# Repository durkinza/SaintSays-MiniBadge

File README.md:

# SAINTSays Mini-Badge

<span style="font-size:0.8em;font-style:italic;">This badge is not made in affiliation with or endorced by the SAINTCON conference or the Utah SAINT organization</span>

This was my first time designing and producing a minibadge for SAINTCON (2024), so it may be a bit rough around the edges.

This repo contains the Code and KiCad file for the SAINTSays Mini-Badge.

## Programming the Badge

Compiling the code in the Arduino IDE for an ATTINY requires a package that supports the `Wire.h` library.

I found that the [ATTINYCore](https://github.com/SpenceKonde/ATTinyCore/blob/v2.0.0-devThis-is-the-head-submit-PRs-against-this/Installation.md) library works well for this. 
If you don't plan on using the I2C features, The [attiny](https://github.com/damellis/attiny) package can also be used for programming the badge. 

The badge has the AREF pins connected to the Mini-Badge headers using the [suggested connection method](https://github.com/lukejenkins/minibadge#prog): 

| Header| Pin |
|-------|-------|
| MISO  | Pin 3 |
| CLK   | Pin 4 |
| MOSI  | Pin 5 |
| RESET | Pin 6 |

The power pin is wired to the 3.3v supply on Pin 7 and ground on Pin 8.

The Clock and SDA/SCL pins are also connected to the ATTiny. 
Be sure these Headers are not connected to external things when programming the badge. 

## Disabling I2C
If you don't plan on using the I2C features of the badbge, the code can be removed by commenting out the `#define USEI2C true` line near the top of the .ino file. 
This has the added benefit of making the compiled code a fair bit smaller too.

## Documentation

[How to solder the badge](https://zanedurk.in/soldering-the-saintsays-mini-badge/)

[How it's made](https://zanedurk.in/saintsays-mini-badge/)

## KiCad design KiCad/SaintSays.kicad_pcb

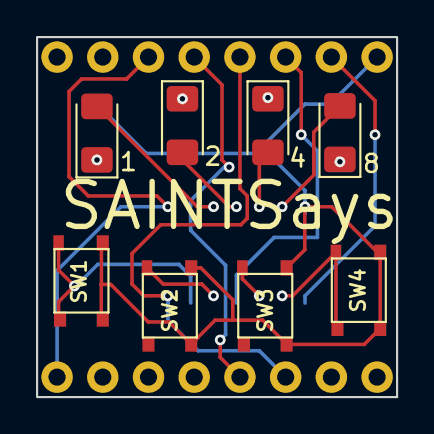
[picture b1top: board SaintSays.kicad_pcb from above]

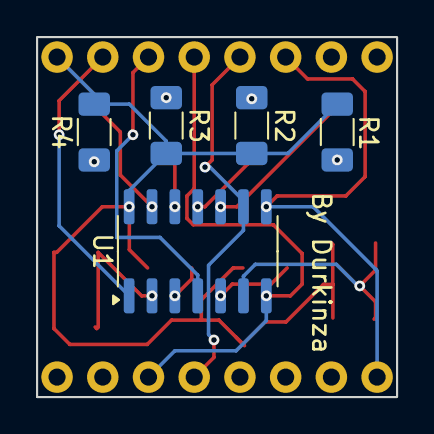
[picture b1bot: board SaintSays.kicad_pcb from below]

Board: 2 copper layers, 20.0 x 20.0 mm, 14 parts (5 on the bottom side), 18 nets.

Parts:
1, 2, 4, 8: LED; LED_1206_3216Metric_Pad1.42x1.75mm_HandSolder
MB1: MiniBadge_SAINTSays; MiniBadge_Full
R1, R2, R3, R4: R_US; R_1206_3216Metric_Pad1.30x1.75mm_HandSolder
SW1, SW2, SW3, SW4: SW_Push; SW_SPST_3x3-L
U1: ATtiny84A-SS; SOIC-14_3.9x8.7mm_P1.27mm

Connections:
unnamed: 1.2 (A), U1.10 (PA3)
unnamed: 1.1 (K), R1.1
unnamed: 2.2 (A), U1.11 (PA2)
unnamed: 2.1 (K), R2.1
unnamed: 4.2 (A), U1.12 (PA1)
unnamed: 4.1 (K), R3.1
unnamed: 8.2 (A), U1.13 (AREF/PA0)
unnamed: 8.1 (K), R4.1
unnamed: MB1.7 (+3V3), U1.1 (VCC)
unnamed: MB1.3 (MISO), MB1.9 (CLK), U1.8 (PA5)
unnamed: MB1.6 (CS), U1.4 (~RESET/PB3)
unnamed: MB1.5 (MOSI), MB1.14 (SDA), U1.7 (PA6)
unnamed: MB1.4 (SCK), MB1.13 (SCL), U1.9 (PA4)
unnamed: MB1.8 (GND), R1.2, R2.2, R3.2, R4.2, SW1.2, SW2.2, SW3.2, SW4.2, U1.14 (GND)
unnamed: SW1.1, U1.6 (PA7)
unnamed: SW2.1, U1.5 (PB2)
unnamed: SW4.1, U1.2 (XTAL1/PB0)
unnamed: SW3.1, U1.3 (XTAL2/PB1)

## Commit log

2024-08-23 Adding V3 code and KiCad
2024-08-23 adding some updates, still working on I2C communication.
2024-08-28 Adding Readme. Updating user guide.
2024-09-10 Adding compiled hex, but it may be best to build from scratch when possible
